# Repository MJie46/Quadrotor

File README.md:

# Quadrotor
>
#### 尺寸50*50mm
#### stm32f405主控
#### 四路SI2302输出
#### 4通道pwm
#### MPU6050
#### 0.96寸OLED接口
#### 板载一个蓝牙模块
#### [IP5306集成电池充放电管理和升压输出](https://github.com/MJie46/Zeeuss)

>
### 软件待完善...

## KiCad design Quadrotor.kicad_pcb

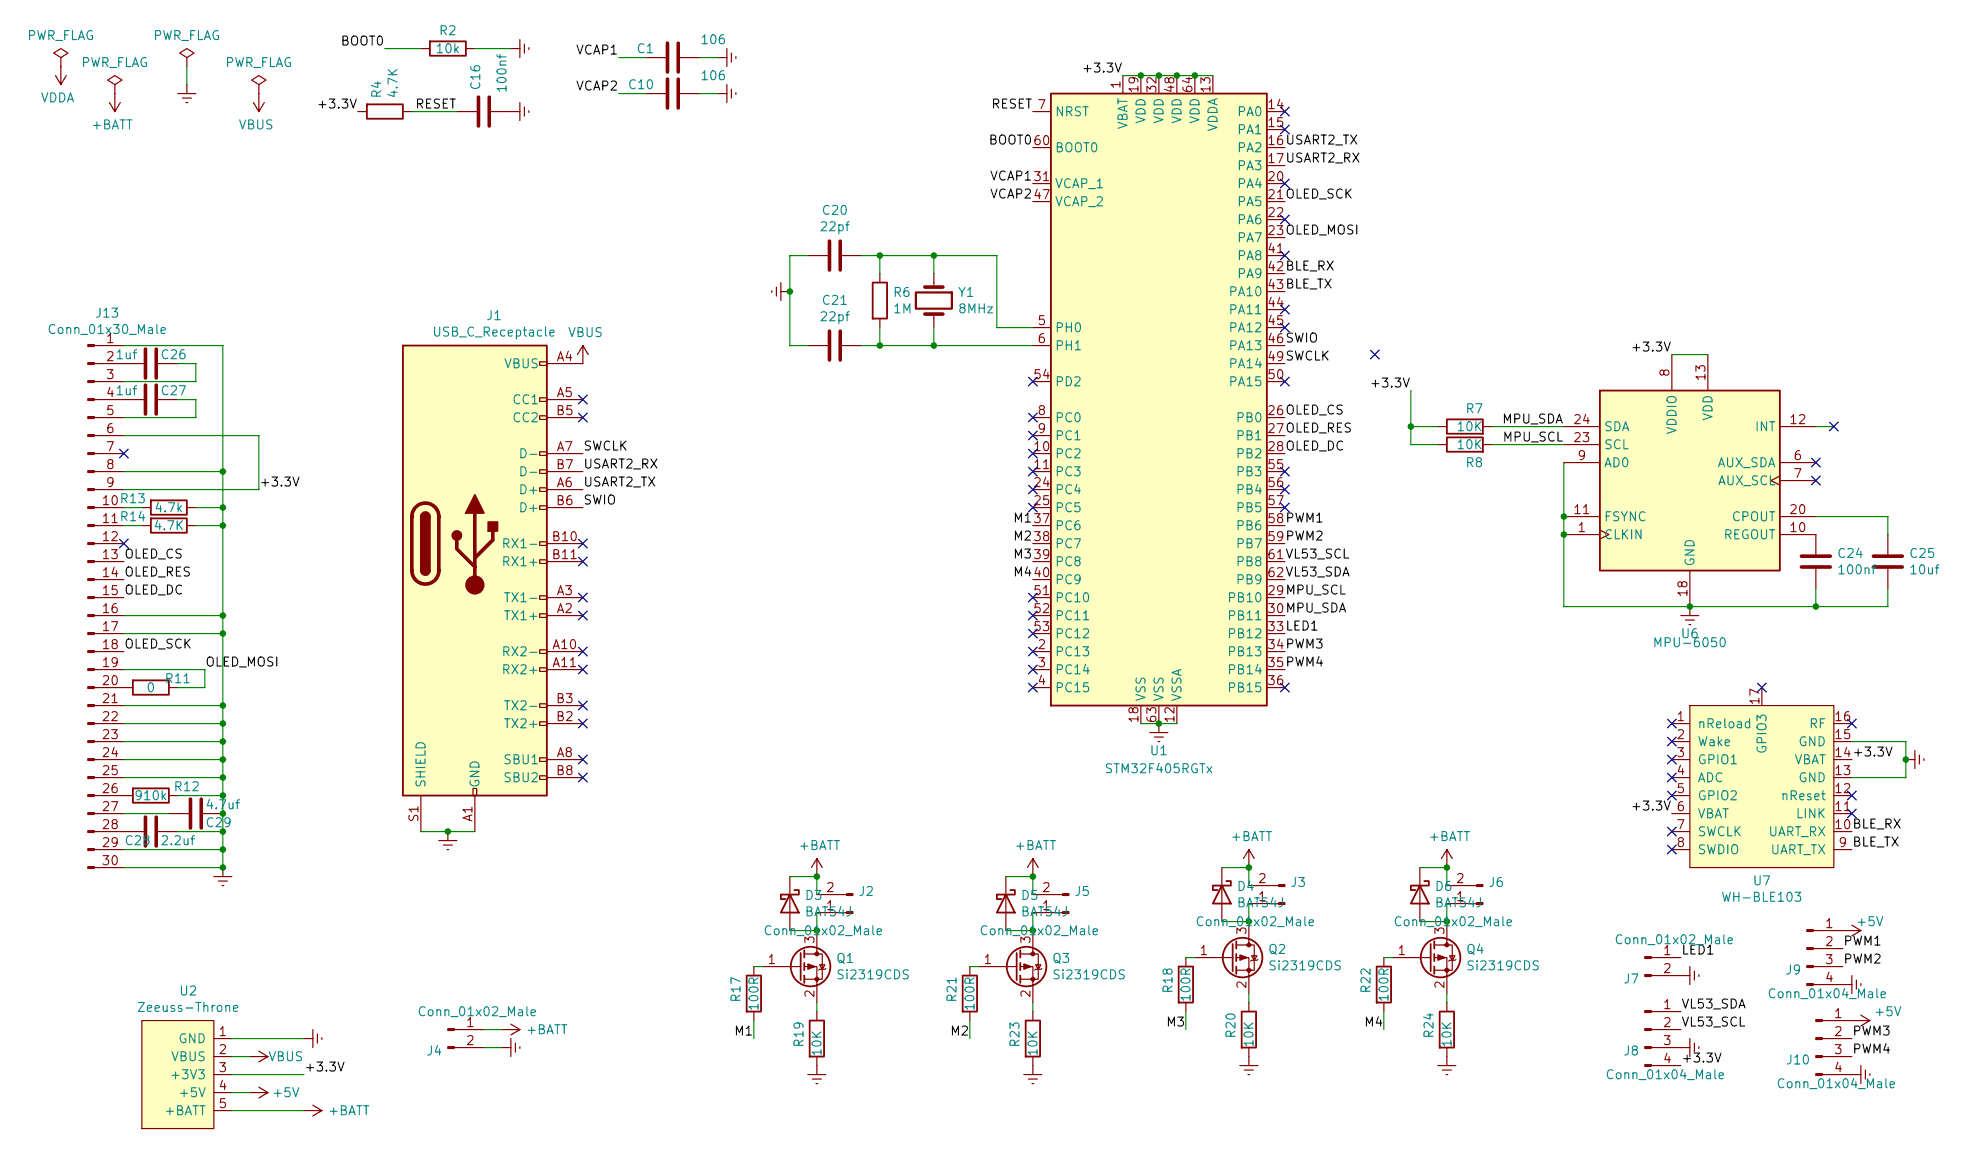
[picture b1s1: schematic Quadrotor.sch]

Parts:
C1, C10: 106; C_0603_1608Metric_Pad1.05x0.95mm_HandSolder
C16, C24: 100nf; C_0603_1608Metric_Pad1.05x0.95mm_HandSolder
C20, C21: 22pf; C_0603_1608Metric_Pad1.05x0.95mm_HandSolder
C25: 10uf; C_0603_1608Metric_Pad1.05x0.95mm_HandSolder
C26, C27: 1uf; C_0603_1608Metric_Pad1.05x0.95mm_HandSolder
C28: 2.2uf; C_0603_1608Metric_Pad1.05x0.95mm_HandSolder
C29: 4.7uf; C_0603_1608Metric_Pad1.05x0.95mm_HandSolder
D3, D4, D5, D6: BAT54J; D_SOD-323F
J1: USB_C_Receptacle; USB_C_Receptacle_XKB_U262-16XN-4BVC11
J2, J3, J4, J5, J6, J7: Conn_01x02_Male; PinHeader_1x02_P2.00mm_Vertical
J8, J9, J10: Conn_01x04_Male; PinHeader_1x04_P2.00mm_Vertical
J13: Conn_01x30_Male; FPC_1x30-0.7mm
Q1, Q2, Q3, Q4: Si2319CDS; SOT-23
R2: 10k; R_0603_1608Metric_Pad1.05x0.95mm_HandSolder
R4, R14: 4.7K; R_0603_1608Metric_Pad1.05x0.95mm_HandSolder
R6: 1M; R_0603_1608Metric_Pad1.05x0.95mm_HandSolder
R7, R8, R19, R20, R23, R24: 10K; R_0603_1608Metric_Pad1.05x0.95mm_HandSolder
R11: 0; R_0603_1608Metric_Pad1.05x0.95mm_HandSolder
R12: 910k; R_0603_1608Metric_Pad1.05x0.95mm_HandSolder
R13: 4.7k; R_0603_1608Metric_Pad1.05x0.95mm_HandSolder
R17, R18, R21, R22: 100R; R_0603_1608Metric_Pad1.05x0.95mm_HandSolder
U1: STM32F405RGTx; LQFP-64_10x10mm_P0.5mm
U2: Zeeuss-Throne; Zeeuss_Throne
U6: MPU-6050; InvenSense_QFN-24_4x4mm_P0.5mm
U7: WH-BLE103
Y1: 8MHz; Crystal_SMD_TXC_7A-2Pin_5x3.2mm

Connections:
+5V: J9.1, J10.1, U2.4 (+5V)
+BATT: D3.1 (K), D4.1 (K), D5.1 (K), D6.1 (K), J2.2, J3.2, J4.1, J5.2, J6.2, U2.5 (+BATT)
/+3.3V: J8.4, J13.6, J13.9, R4.2, R7.1, R8.1, U1.1 (VBAT), U1.13 (VDDA), U1.19 (VDD), U1.32 (VDD), U1.48 (VDD), U1.64 (VDD), U2.3 (+3V3), U6.8 (VDDIO), U6.13 (VDD), U7.6 (VBAT), U7.14 (VBAT)
/BLE_RX: U1.42 (PA9), U7.10 (UART_RX)
/BLE_TX: U1.43 (PA10), U7.9 (UART_TX)
/BOOT0: R2.2, U1.60 (BOOT0)
/LED1: J7.1, U1.33 (PB12)
/M1: R17.2, U1.37 (PC6)
/M2: R21.2, U1.38 (PC7)
/M3: R18.2, U1.39 (PC8)
/M4: R22.2, U1.40 (PC9)
/MPU_SCL: R8.2, U1.29 (PB10), U6.23 (SCL)
/MPU_SDA: R7.2, U1.30 (PB11), U6.24 (SDA)
/OLED_CS: J13.13, U1.26 (PB0)
/OLED_DC: J13.15, U1.28 (PB2)
/OLED_MOSI: J13.19, R11.1, U1.23 (PA7)
/OLED_RES: J13.14, U1.27 (PB1)
/OLED_SCK: J13.18, U1.21 (PA5)
/PWM1: J9.2, U1.58 (PB6)
/PWM2: J9.3, U1.59 (PB7)
/PWM3: J10.2, U1.34 (PB13)
/PWM4: J10.3, U1.35 (PB14)
/RESET: C16.1, R4.1, U1.7 (NRST)
/SWCLK: J1.A7 (D-), U1.49 (PA14)
/SWIO: J1.B6 (D+), U1.46 (PA13)
/USART2_RX: J1.B7 (D-), U1.17 (PA3)
/USART2_TX: J1.A6 (D+), U1.16 (PA2)
/VCAP1: C1.1, U1.31 (VCAP_1)
/VCAP2: C10.1, U1.47 (VCAP_2)
/VL53_SCL: J8.2, U1.61 (PB8)
/VL53_SDA: J8.1, U1.62 (PB9)
Earth: C1.2, C10.2, C16.2, C20.2, C21.2, C24.2, C25.2, C28.1, C29.1, J1.A1 (GND), J1.A12 (GND), J1.B1 (GND), J1.B12 (GND), J1.S1 (SHIELD), J4.2, J7.2, J8.3, J9.4, J10.4, J13.1, J13.8, J13.16, J13.17, J13.21, J13.22, J13.23, J13.24, J13.25, J13.29, J13.30, R2.1, R12.1, R13.1, R14.1, R19.2, R20.2, R23.2, R24.2, U1.12 (VSSA), U1.18 (VSS), U1.63 (VSS), U2.1 (GND), U6.1 (CLKIN), U6.9 (AD0), U6.11 (FSYNC), U6.18 (GND), U7.13 (GND), U7.15 (GND)
unnamed: C20.1, R6.1, U1.5 (PH0), Y1.1
unnamed: C21.1, R6.2, U1.6 (PH1), Y1.2
unnamed: C24.1, U6.10 (REGOUT)
unnamed: C25.1, U6.20 (CPOUT)
unnamed: C26.1, J13.3
unnamed: C26.2, J13.2
unnamed: C27.1, J13.5
unnamed: C27.2, J13.4
unnamed: C28.2, J13.28
unnamed: C29.2, J13.27
unnamed: D3.2 (A), J2.1, Q1.3 (D)
unnamed: D4.2 (A), J3.1, Q2.3 (D)
unnamed: D5.2 (A), J5.1, Q3.3 (D)
unnamed: D6.2 (A), J6.1, Q4.3 (D)
unnamed: J13.10, R13.2
unnamed: J13.11, R14.2
unnamed: J13.20, R11.2
unnamed: J13.26, R12.2
unnamed: Q1.1 (G), R17.1
unnamed: Q1.2 (S), R19.1
unnamed: Q2.1 (G), R18.1
unnamed: Q2.2 (S), R20.1
unnamed: Q3.1 (G), R21.1
unnamed: Q3.2 (S), R23.1
unnamed: Q4.1 (G), R22.1
unnamed: Q4.2 (S), R24.1
VBUS: J1.A4 (VBUS), J1.A9 (VBUS), J1.B4 (VBUS), J1.B9 (VBUS), U2.2 (VBUS)

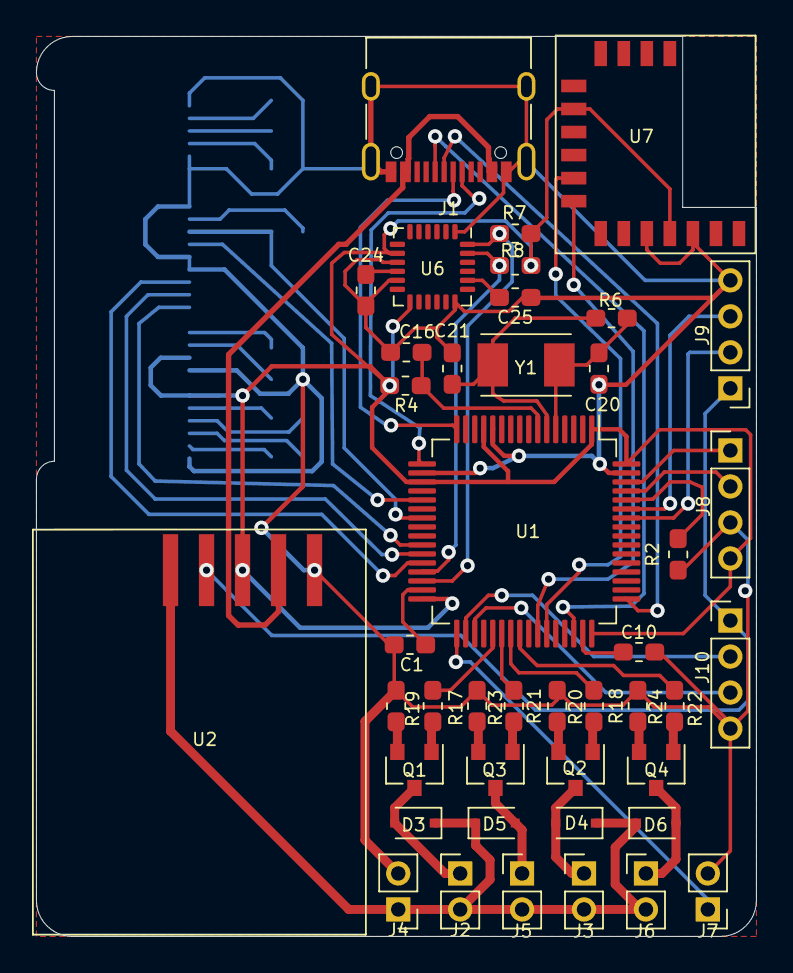
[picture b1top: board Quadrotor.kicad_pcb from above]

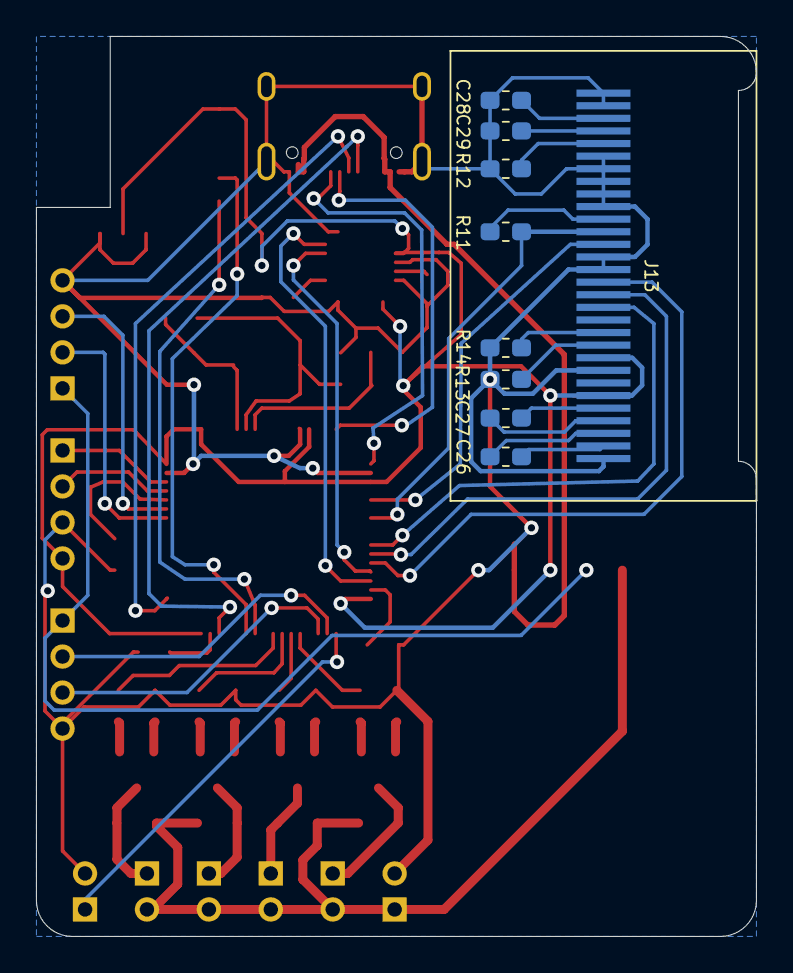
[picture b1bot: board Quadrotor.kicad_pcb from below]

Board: 2 copper layers, 40.0 x 50.0 mm, 52 parts (9 on the bottom side), 59 nets.

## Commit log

2020-11-30 add readme
2020-12-18 修改pcb文件
